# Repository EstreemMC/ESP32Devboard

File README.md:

# ESP32Devboard
A custom esp32 devboard with traces for all buttons and potentiometer inputs. Integrated with another esp32 and a GC+2 from 4layertech to emulate a gamecube controller on supported hardware(Wii/Gamecube).

I first needed to consider applications of the MCU. I'm using a GC +2.0 gamecube controller emulator from 4layer tech.

To access my required button features, I determined it necessary to use 17 IO pins for a combination of digital and PWM outputs. For my vibration motors, I needed to figure out if they required digital or analog input. Researching the electrical diagram for the motor controller on the GC+2.0 showed that PWM was used for the controls as well, allowing me to directly tap the PWM and feed it through an ESP32 IO input.

For flash memory access, I decided to implement the USB-C spec. The ESP32 has D+ and D- pins that can directly interface with it.

To drive the motors wirelessly, a small motor controller would be required. I decided on the L293D, since its easily implementable, has a small footprint, and has the ability to control more than 1 motor if I would need it in the future.

Gamecube controller rumble motors draw 5v or 3.3v. For the current draw on the 3.3v line, the controller requires a max of 1.5A. Standard voltage regulators cannot supply this, so I had to spring for a high-end 2A voltage regulator. There wasn't much documentation, so I had to mimic the standard circuit provided in the datasheet; mostly standard, with power lines connected to decoupling capacitors which bypass to ground.

For interfacing and troubleshooting components, I added 3 status LEDs(3.3v test, 5v test, blink/file upload) as well as 40 pins.

Boot and reset buttons were standard, pulling EN high and pulling IO0 low.

Finally, for wireless low latency capabilities, I decided on using ESPNOW as a communication protocol, requiring antenna access on the module.

With the rough layout completed of what I would need, I drafted a schematic using the ESP32 schematic checklist and external open source schematics. Be aware if you are replicating that the voltage regulator VOUT sense is marked as an output instead of an input on the TI symbol; ERC will throw an error, its the symbol's fault, shouldn't be an issue.

The footprint for the USB-C port in KiCad for the M-12 USB C is faulty, you need to download a revised version from the manufacturer. The mechanical holes only have .2mm clearance as well, so I shrunk some of the pads on the final pcb to account for this.

With the schematic done, I began to lay out the PCB. Organization was fairly self-explanatory, with my goal to minimize overlapping traces and minimizing space between pins and decoupling capacitors/pulldown resistors. Because of the compact nature of my board, as well as integration for 5v and 3.3v circuits, I decided to use a 4 layer board to maximize signal integrity. Layer 1 was for signal wires and short power connections, layer 2 was my ground plane, layer 3 was a mix of 3.3v copper fill and 5v fill, and layer 4 was for aux connections. Figuring out layer 3 was the biggest hurdle, since I wasn't able to overlap 3.3v and 5v traces, including signal wires. I had to minimize signal traces moving over fill boundaries as well. After some work, I managed to get a decent arrangement to start routing.

I prioritized USB-C signal integrity by mapping the data pins as a differential pair.

Because of the nature of the board as a 4 layer, I was able to have easy trace management with little overlap. The power and ground planes allowed me to just connect through-hole vias to any 3v3, 5v, and GND(with the exemption of those needing pulldowns or decoupling). Notably, I needed to swap my motor PS capacitor for a bulk capacitor due to its potentially high impact on PWM motor signal integrity. Routing all the traces got me this finished board.

Because of the variety of parts outside the JLCPCB and KiCad standard parts library, and due to component shortages by JLCPCB, many components needed off-market alternatives, like the LEDs and my bulk capacitor. Notable choice was to use the n16 model of the ESP-32 for high flash storage(macro/recall).

JLCPCB CAD Viewer(USBC and ESP are offset for some reason, pins line up but apparently its an issue that gets fixed in DFM).

Overall, the project turned out really well for a first time PCB. I had little to no references for my requirements, but I managed to actually make something that could work! No errors in ERC(except aforementioned ignore) or DRC, just warnings for cosmetic errors, isolated copper fills, and reference errors to the standard footprint library since I edited the footprints. Practically everything follows the recommended spec from manufacturer datasheets.

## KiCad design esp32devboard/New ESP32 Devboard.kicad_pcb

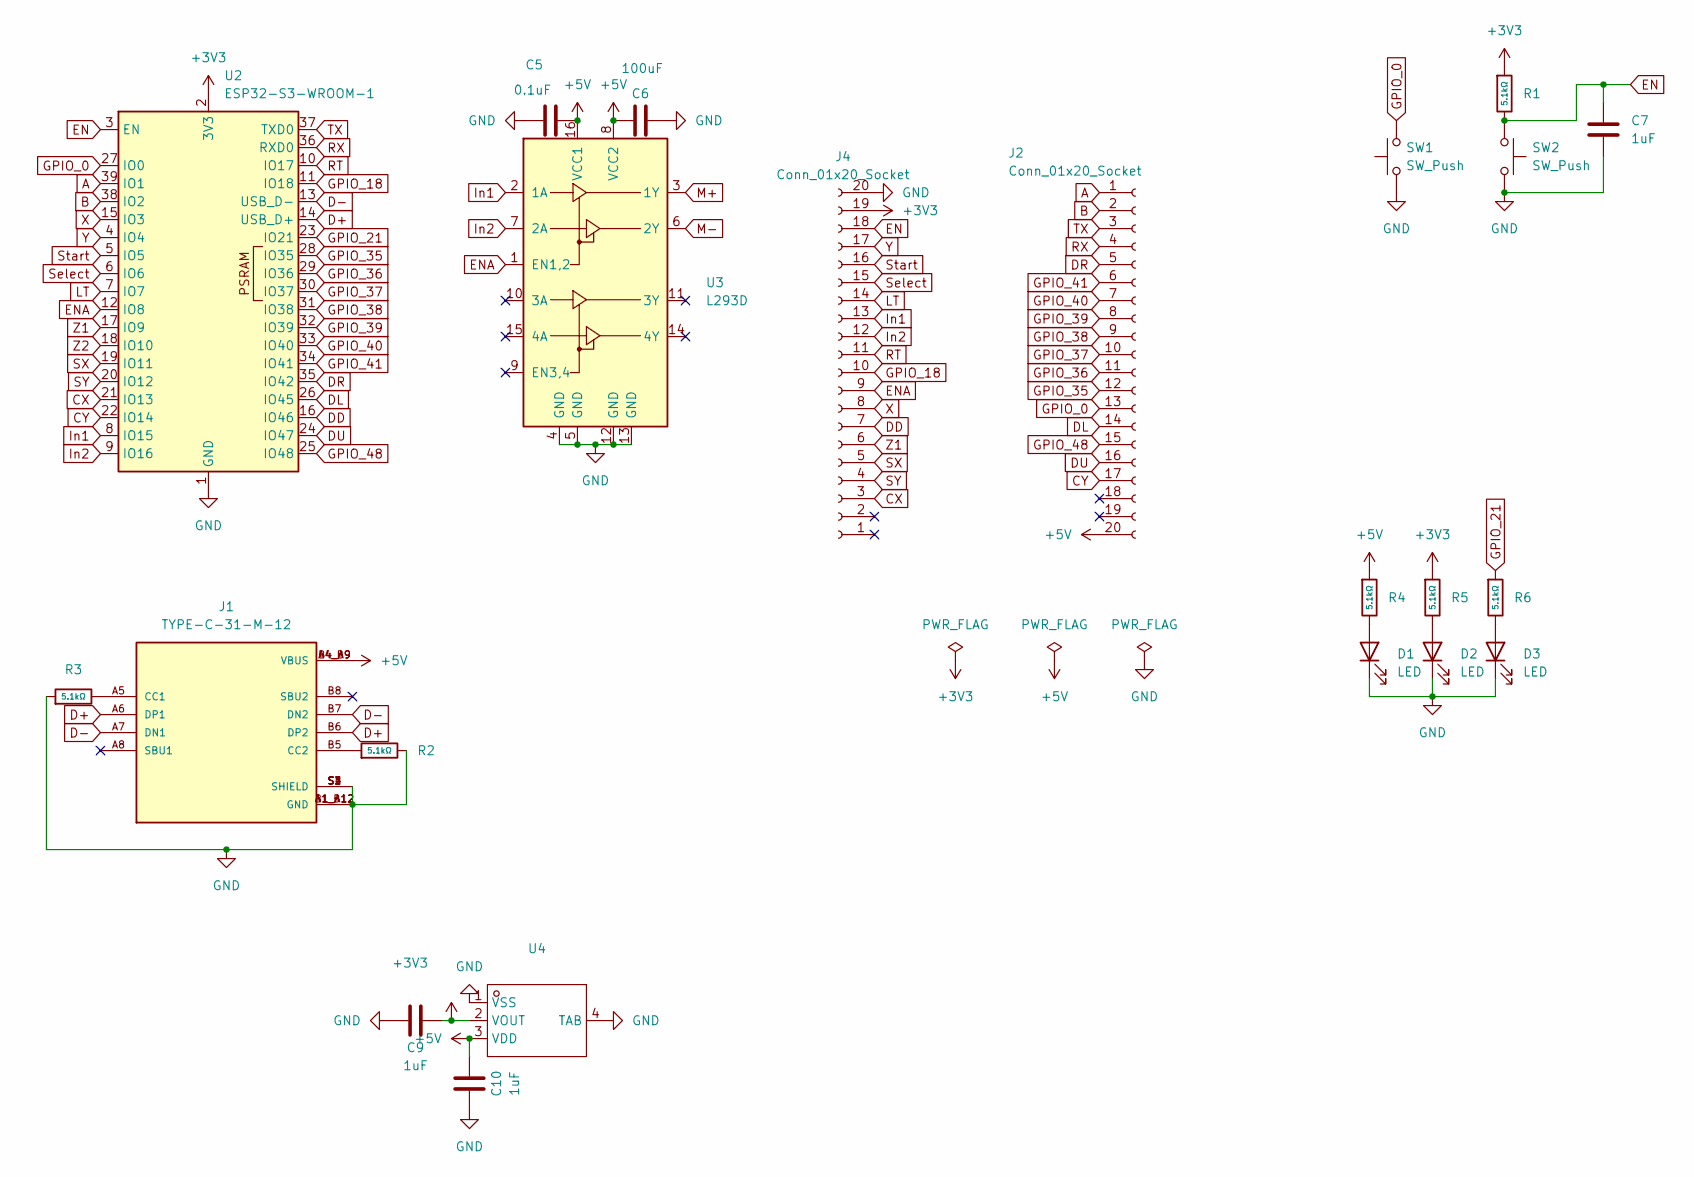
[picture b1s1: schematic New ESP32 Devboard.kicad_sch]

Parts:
C5: 0.1uF; C_0603_1608Metric
C6: 100uF; C_0603_1608Metric
C7, C9, C10: 1uF; C_0603_1608Metric
D1, D2, D3: LED; LED_0603_1608Metric
J1: TYPE-C-31-M-12; Updated_TYPE-C-31-M-12; PARTREV 2020.12.08
J2, J4: Conn_01x20_Socket; PinHeader_1x20_P2.54mm_Vertical
R1, R2, R3, R4, R5, R6: 5.1kΩ; R_0603; Overload Voltage (Max) 75V; Tolerance ±1%; Part 0603WAF5101T5E; LCSC C23186
SW1, SW2: SW_Push; SW_SPST_B3S-1100
U2: ESP32-S3-WROOM-1
U3: L293D; DIP-16_W7.62mm
U4: bl8072; Manufacturer Part BL8072CLTR33; LCSC Part Name 2A低功耗线性稳压器

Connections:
+3V3: C9.1, J4.19, R1.1, R5.1, U2.2 (3V3), U4.2 (VOUT)
+5V: C5.1, C6.1, C10.1, J1.A4_B9 (VBUS), J1.B4_A9 (VBUS), J2.20, R4.1, U3.8 (VCC2), U3.16 (VCC1), U4.3 (VDD)
A: J2.1, U2.39 (IO1)
B: J2.2, U2.38 (IO2)
CX: J4.3, U2.21 (IO13)
CY: J2.17, U2.22 (IO14)
D+: J1.A6 (DP1), J1.B6 (DP2), U2.14 (USB_D+)
D-: J1.A7 (DN1), J1.B7 (DN2), U2.13 (USB_D-)
DD: J4.7, U2.16 (IO46)
DL: J2.14, U2.26 (IO45)
DR: J2.5, U2.35 (IO42)
DU: J2.16, U2.24 (IO47)
EN: C7.2, J4.18, R1.2, SW2.1, U2.3 (EN)
ENA: J4.9, U2.12 (IO8), U3.1 (EN1,2)
GND: C5.2, C6.2, C7.1, C9.2, C10.2, D1.1 (K), D2.1 (K), D3.1 (K), J1.A1_B12 (GND), J1.B1_A12 (GND), J1.S1 (SHIELD), J1.S2 (SHIELD), J1.S3 (SHIELD), J1.S4 (SHIELD), J4.20, R2.2, R3.1, SW1.1, SW2.2, U2.1 (GND), U2.40 (GND), U2.41 (GND), U3.4 (GND), U3.5 (GND), U3.12 (GND), U3.13 (GND), U4.1 (VSS), U4.4 (TAB)
GPIO_0: J2.13, SW1.2, U2.27 (IO0)
GPIO_18: J4.10, U2.11 (IO18)
GPIO_21: R6.1, U2.23 (IO21)
GPIO_35: J2.12, U2.28 (IO35)
GPIO_36: J2.11, U2.29 (IO36)
GPIO_37: J2.10, U2.30 (IO37)
GPIO_38: J2.9, U2.31 (IO38)
GPIO_39: J2.8, U2.32 (IO39)
GPIO_40: J2.7, U2.33 (IO40)
GPIO_41: J2.6, U2.34 (IO41)
GPIO_48: J2.15, U2.25 (IO48)
In1: J4.13, U2.8 (IO15), U3.2 (1A)
In2: J4.12, U2.9 (IO16), U3.7 (2A)
LT: J4.14, U2.7 (IO7)
M+: U3.3 (1Y)
M-: U3.6 (2Y)
unnamed: D1.2 (A), R4.2
unnamed: D2.2 (A), R5.2
unnamed: D3.2 (A), R6.2
unnamed: J1.A5 (CC1), R3.2
unnamed: J1.B5 (CC2), R2.1
RT: J4.11, U2.10 (IO17)
RX: J2.4, U2.36 (RXD0)
SX: J4.5, U2.19 (IO11)
SY: J4.4, U2.20 (IO12)
Select: J4.15, U2.6 (IO6)
Start: J4.16, U2.5 (IO5)
TX: J2.3, U2.37 (TXD0)
X: J4.8, U2.15 (IO3)
Y: J4.17, U2.4 (IO4)
Z1: J4.6, U2.17 (IO9)
Z2: U2.18 (IO10)

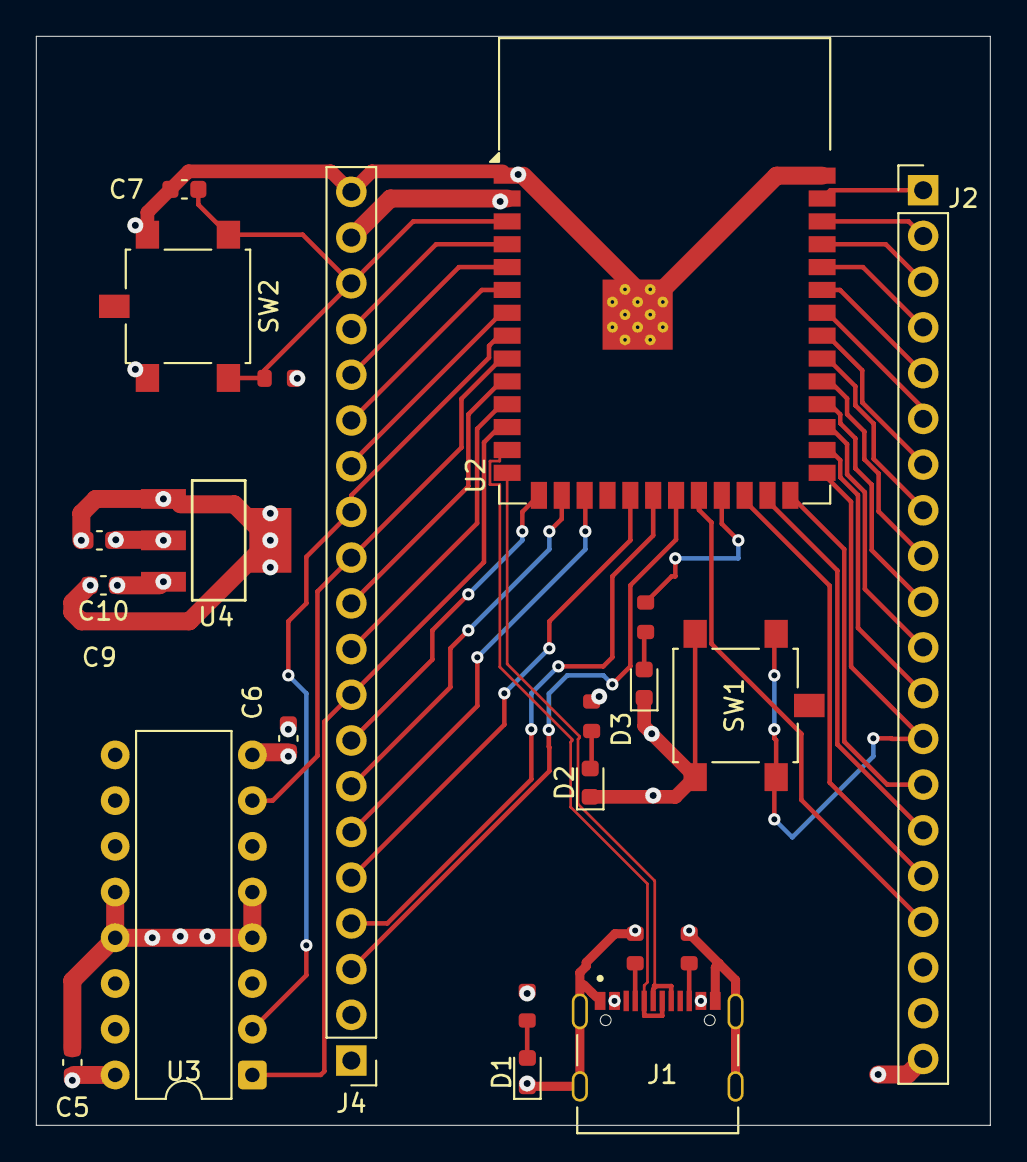
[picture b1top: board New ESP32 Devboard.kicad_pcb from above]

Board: 4 copper layers, 53.0 x 60.5 mm, 22 parts (0 on the bottom side), 44 nets.

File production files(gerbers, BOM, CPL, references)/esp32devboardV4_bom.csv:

Designator,Footprint,Quantity,Value,LCSC Part #
"C10, C7, C9",0603,3,1uF,
C5,0603,1,0.1uF,
C6,0603,1,100uF,
"D1, D2, D3",0603,3,LED,
J1,Updated_TYPE-C-31-M-12,1,TYPE-C-31-M-12,
"J2, J4",PinHeader_1x20_P2.54mm_Vertical,2,Conn_01x20_Socket,
"R1, R2, R3, R4, R5, R6",R_0603,6,5.1kΩ,C23186
"SW1, SW2",SW_SPST_B3S-1100,2,SW_Push,
U2,ESP32-S3-WROOM-1,1,ESP32-S3-WROOM-1,
U3,DIP-16_W7.62mm,1,L293D,
U4,bl8072,1,~,
